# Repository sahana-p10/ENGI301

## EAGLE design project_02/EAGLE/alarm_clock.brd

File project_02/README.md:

# Alarm Clock PCB 

This project is based off my project 1 for this class. It creates a PCB for the alarm clock portion. 

The repository includes a pdf schematic, all the EAGLE files (library, schematic, board), and additional manufacturing files such as CAM, gerbers, and bill of materials, in the MFG and implementation folder.

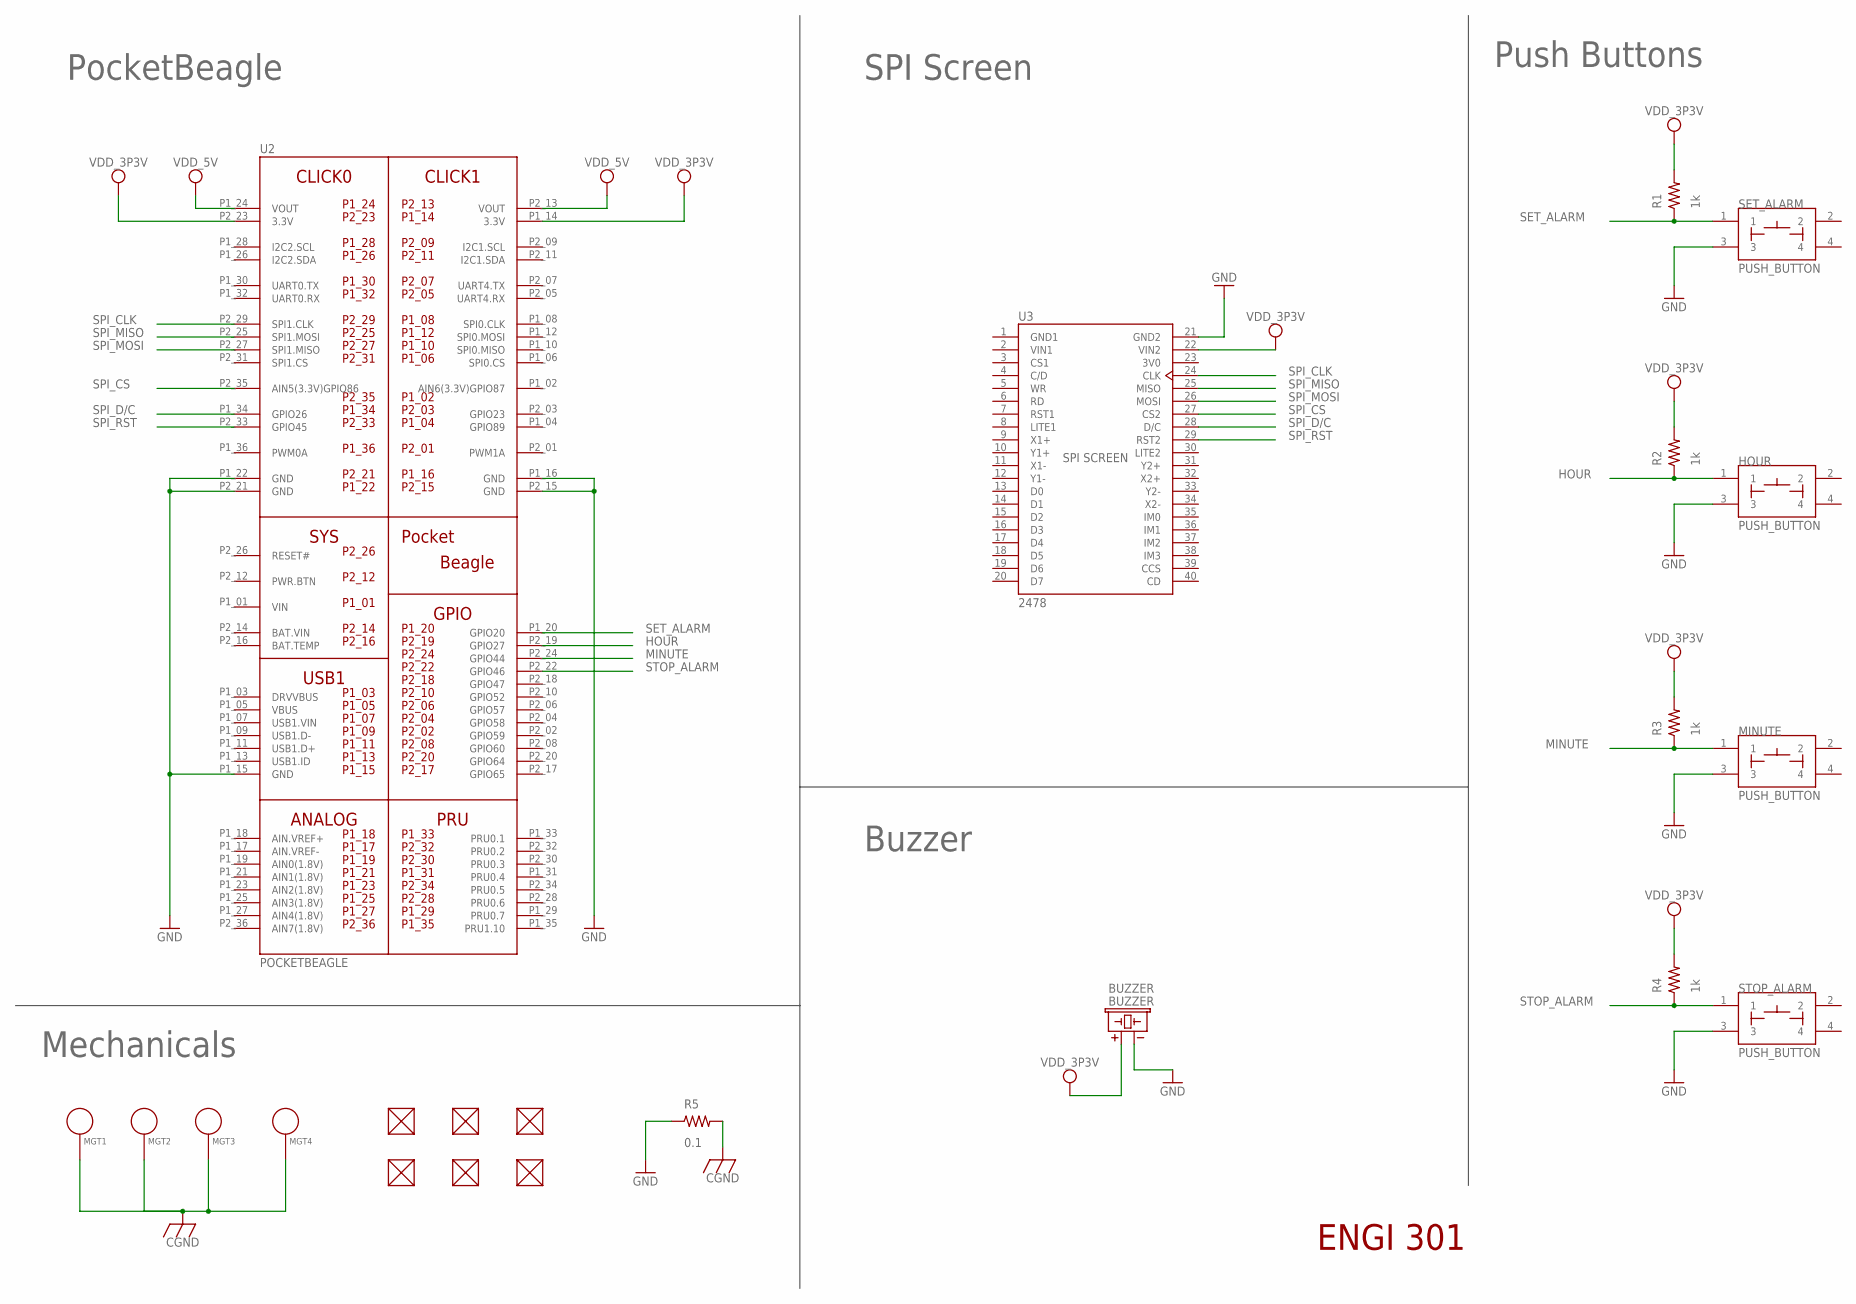
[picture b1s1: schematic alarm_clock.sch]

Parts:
BUZZER: BUZZER; BUZZER_6.5MM
FUD1, FUD2, FUD3, FUD4, FUD5, FUD6: FIDUCIAL; FIDUCIAL_40MIL
HOUR: PUSH_BUTTON; BUTTON_12.5MM
MGT1, MGT2, MGT3, MGT4: MOUNTING_HOLE
MINUTE: PUSH_BUTTON; BUTTON_12.5MM
R1, R2, R3, R4: 1k; R0603
R5: 0.1; R0402
SET_ALARM: PUSH_BUTTON; BUTTON_12.5MM
STOP_ALARM: PUSH_BUTTON; BUTTON_12.5MM
U2: POCKETBEAGLE
U3: 2478; ADAFRUIT_2478

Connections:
BAT.VIN: U2.P2_14 (BAT.VIN)
CGND: MGT1.P$1, MGT2.P$1, MGT3.P$1, MGT4.P$1, R5.2
GND: BUZZER.-, HOUR.3, MINUTE.3, R5.1, SET_ALARM.3, STOP_ALARM.3, U2.P1_15 (GND), U2.P1_16 (GND), U2.P1_22 (GND), U2.P2_15 (GND), U2.P2_21 (GND), U3.21 (GND2)
GND1: U3.1 (GND1)
HOUR: HOUR.1, R2.1, U2.P2_19 (GPIO27)
MINUTE: MINUTE.1, R3.1, U2.P2_24 (GPIO44)
SET_ALARM: R1.1, SET_ALARM.1, U2.P1_20 (GPIO20)
SPI_CLK: U2.P2_29 (SPI1.CLK), U3.24 (CLK)
SPI_CS: U2.P2_35 (AIN5(3.3V)GPIO86), U3.27 (CS2)
SPI_D/C: U2.P1_34 (GPIO26), U3.28 (D/C)
SPI_MISO: U2.P2_25 (SPI1.MOSI), U3.25 (MISO)
SPI_MOSI: U2.P2_27 (SPI1.MISO), U3.26 (MOSI)
SPI_RST: U2.P2_33 (GPIO45), U3.29 (RST2)
STOP_ALARM: R4.1, STOP_ALARM.1, U2.P2_22 (GPIO46)
VDD_3P3V: BUZZER.+, R1.2, R2.2, R3.2, R4.2, U2.P1_14 (3.3V), U2.P2_23 (3.3V), U3.22 (VIN2)
VDD_5V: U2.P1_24 (VOUT), U2.P2_13 (VOUT)
VIN: U2.P1_01 (VIN)
VIN1: U3.2 (VIN1)

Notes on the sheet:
PocketBeagle
SPI Screen
Buzzer
Push Buttons
Mechanicals
ENGI 301

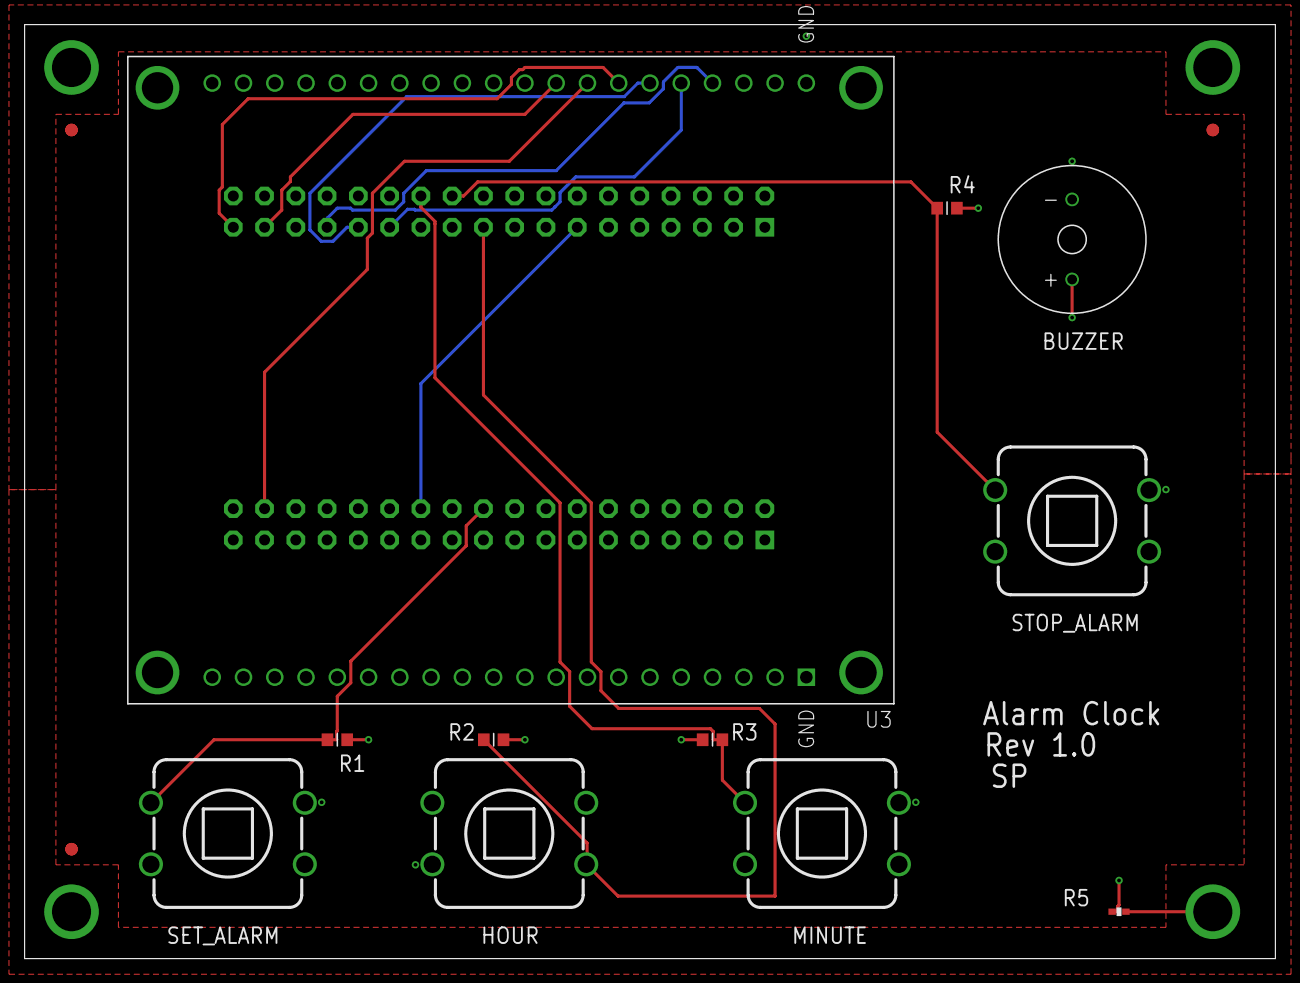
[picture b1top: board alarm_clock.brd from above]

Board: 4 copper layers, 101.6 x 75.9 mm, 22 parts (1 on the bottom side), 14 nets.

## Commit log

2023-12-12 Create blank
